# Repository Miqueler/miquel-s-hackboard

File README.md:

# Miquel's Macroboard

This is my 4 key macropad with 2 SK6812MINI Leds, and uses KMK firmware

## Features:
- 2 SK6812MINI  LEDs. 
- 4 Keys

## CAD Model:
It has 2 separate printed pieces. The base where the PCB sits, and the top cover. 

Made in Fusion360. 

## PCB
Here's my PCB! It was made in KiCad. 

Schematic

PCB

## Firmware Overview
This hackpad uses [KMK]([https://kmk.fm/](https://github.com/KMKfw/kmk_firmware)) firmware for everything. 

- The 4 keys currently act as macros.

I might add more in the future! That's it for now but this has been a cool learning experience, a way to start to dabble into this world of design, both for the PBC design part of things as well as the 3d modeling!

## BOM:
Here should be everything you need to make this hackpad

- 4x Cherry MX Switches
- 4x DSA Keycaps
- 2x SK6812MINI LEDs
- 1x 0.91" 128x32 OLED Display
- 1x XIAO RP2040
- 1x Case (2 printed parts)

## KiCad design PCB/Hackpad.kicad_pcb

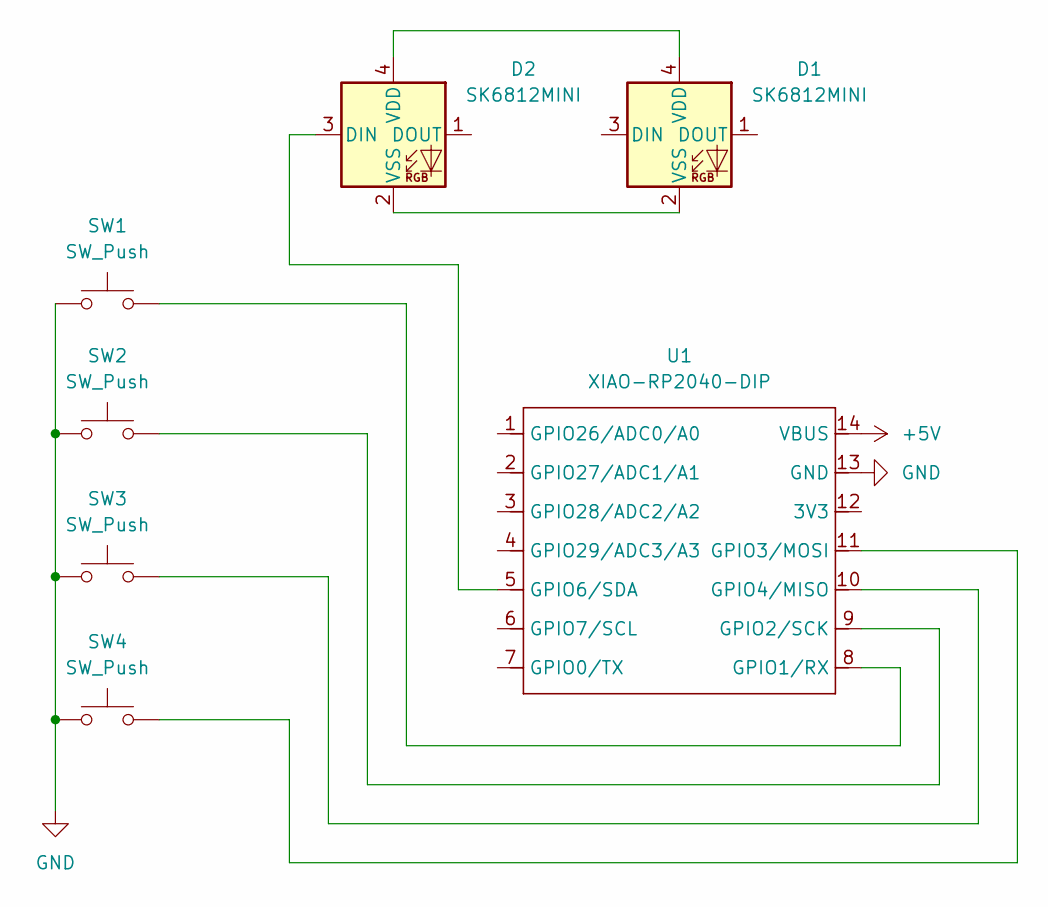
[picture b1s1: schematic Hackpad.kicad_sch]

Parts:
D1, D2: SK6812MINI; LED_SK6812MINI_PLCC4_3.5x3.5mm_P1.75mm
SW1, SW2, SW3, SW4: SW_Push; SW_Cherry_MX_1.00u_PCB
U1: XIAO-RP2040-DIP

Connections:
+5V: U1.14 (VBUS)
GND: SW1.1, SW2.1, SW3.1, SW4.1, U1.13 (GND)
unnamed: D1.4 (VDD), D2.4 (VDD)
unnamed: D1.2 (VSS), D2.2 (VSS)
unnamed: D2.3 (DIN), U1.5 (GPIO6/SDA)
unnamed: SW1.2, U1.8 (GPIO1/RX)
unnamed: SW2.2, U1.9 (GPIO2/SCK)
unnamed: SW4.2, U1.11 (GPIO3/MOSI)
unnamed: SW3.2, U1.10 (GPIO4/MISO)

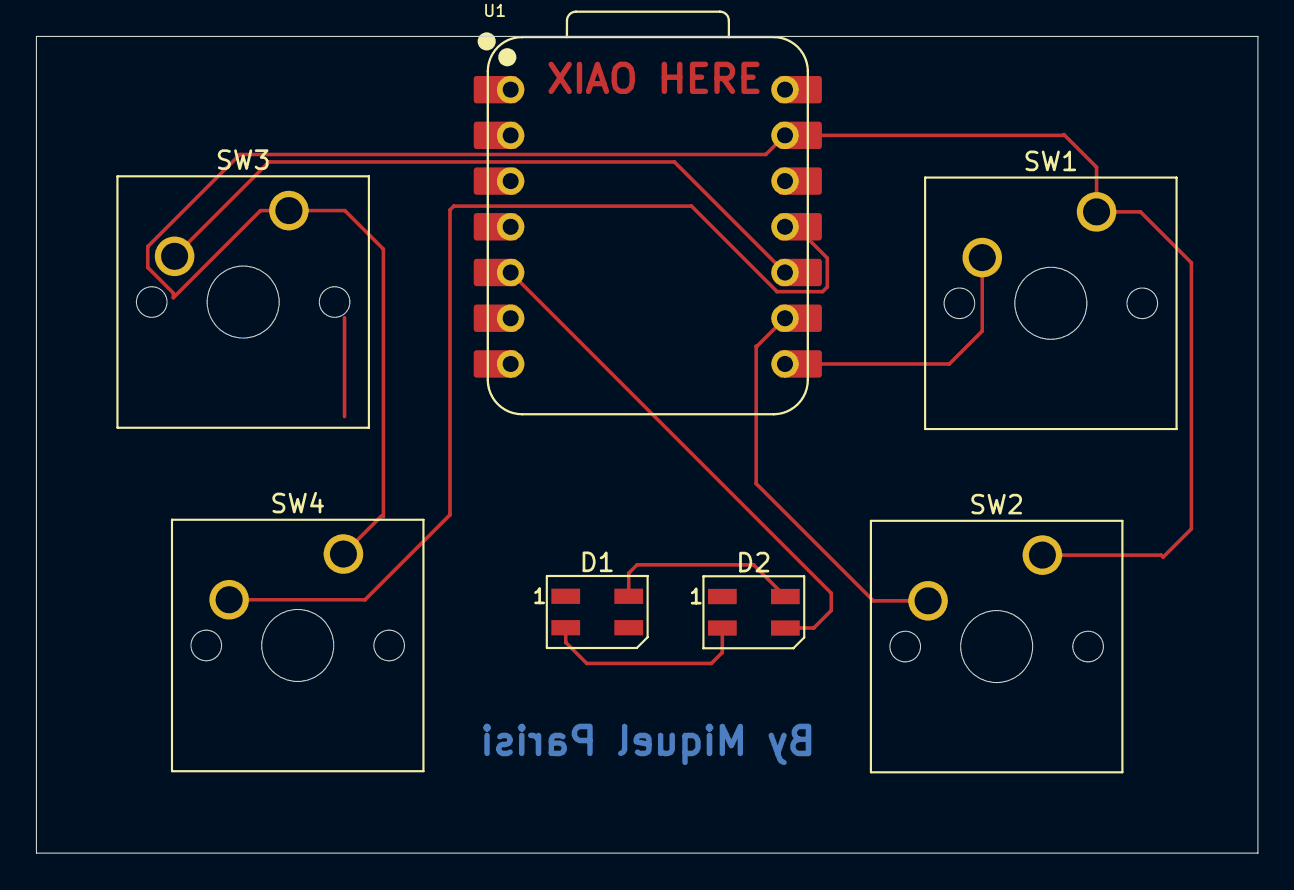
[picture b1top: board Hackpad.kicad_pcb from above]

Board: 2 copper layers, 67.9 x 45.4 mm, 7 parts (0 on the bottom side), 8 nets.

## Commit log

2025-12-04 Rename project to Orpheuspad and enhance README
    Updated project name and added detailed descriptions of features, CAD model, PCB, firmware overview, BOM, and extra information.
2025-12-04 Revise README for Miquel's Macroboard details
    Updated project name and specifications in README.
2025-12-04 Rename Captura de pantalla 2025-12-04 a las 23.34.13.png to pcb.png
2025-12-04 Rename Captura de pantalla 2025-12-04 a las 23.35.10.png to schematic.png
2025-12-05 Rename Hackpad.kicad_pcb to PCB/Hackpad.kicad_pcb
2025-12-05 Rename Hackpad.kicad_pro to PCB/Hackpad.kicad_pro
2025-12-05 Rename Hackpad.kicad_sch to PCB/Hackpad.kicad_sch
2025-12-05 Rename assembled_case.step to CAD/assembled_case.step
2025-12-05 Rename main.py to Firmware/main.py
